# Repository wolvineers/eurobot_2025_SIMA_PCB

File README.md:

# eurobot_2025_SIMA_PCB
Repository of the eurobot 2025 SIMA's PCB

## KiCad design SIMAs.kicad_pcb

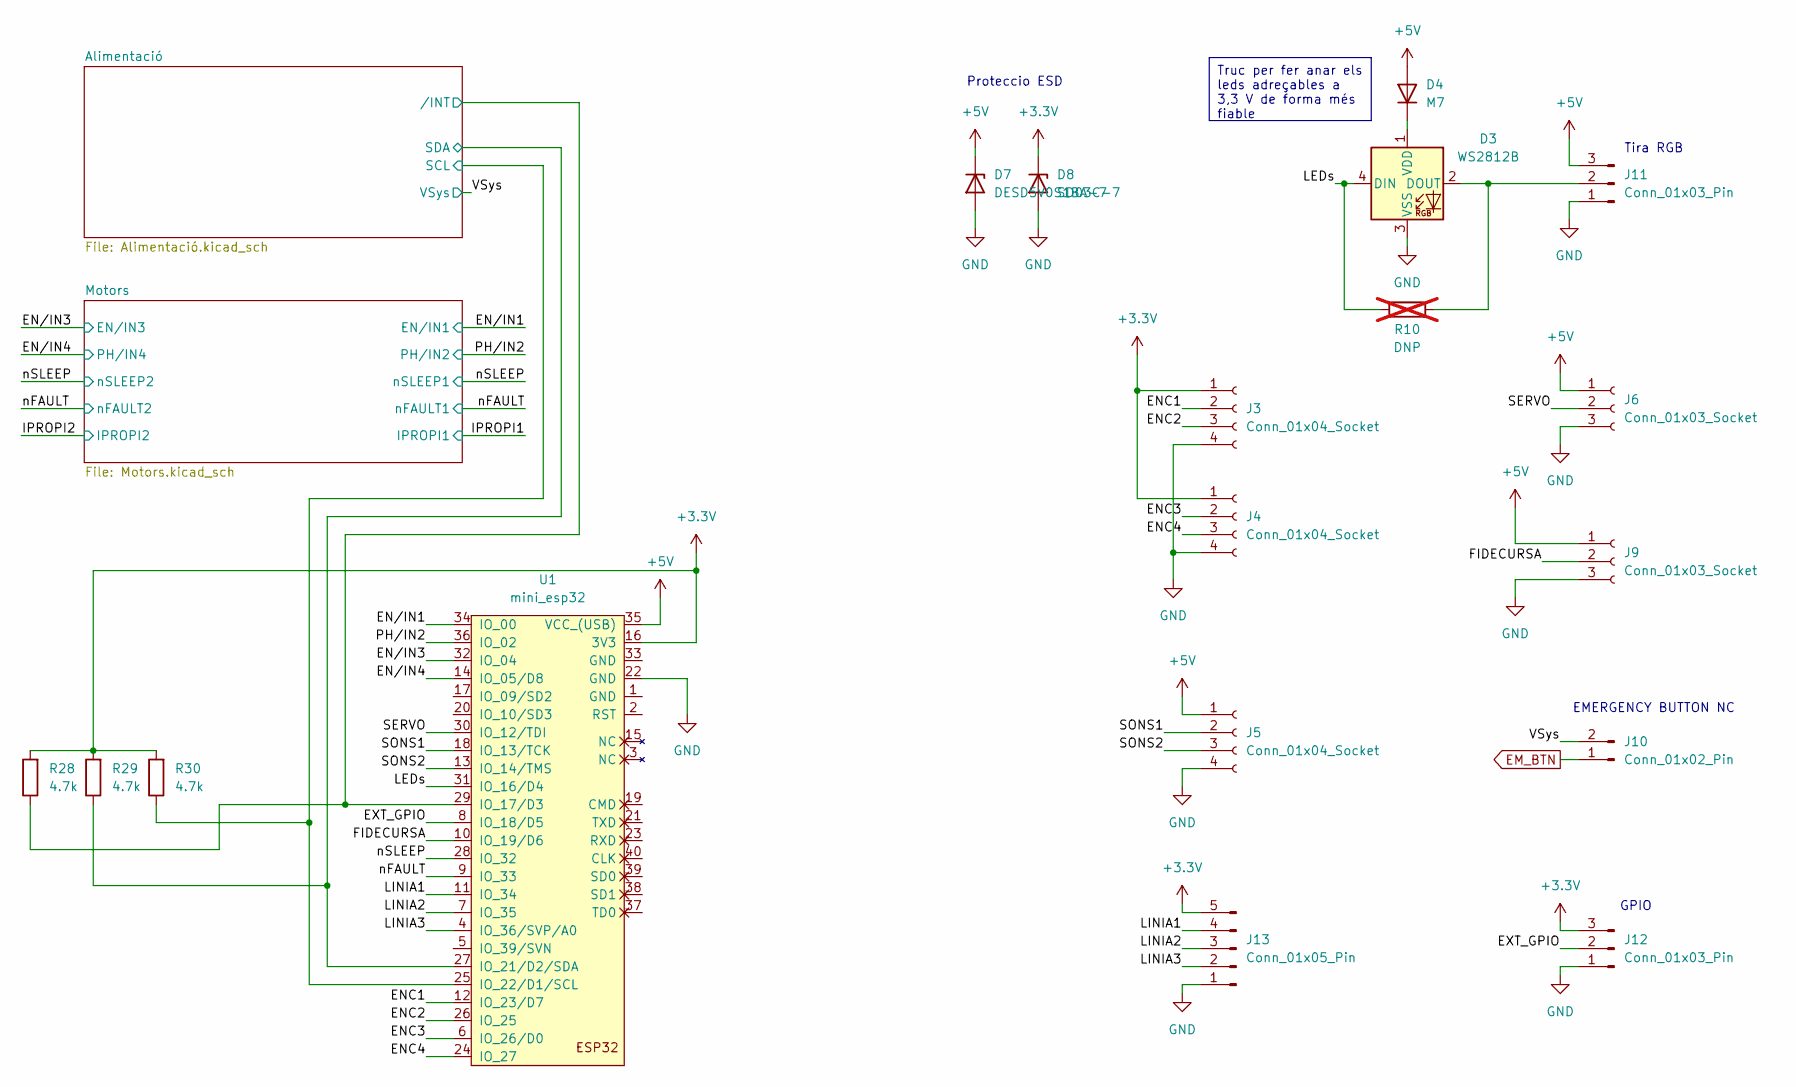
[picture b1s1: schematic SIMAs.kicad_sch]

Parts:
D3: WS2812B; LED_WS2812B_PLCC4_5.0x5.0mm_P3.2mm
D4: M7; D_SMA_Handsoldering
D7: DESD5V0S1BA-7; D_SOD-323
D8: SD03C-7; D_SOD-323
J3, J4, J5: Conn_01x04_Socket; JST_PH_B4B-PH-K_1x04_P2.00mm_Vertical
J6, J9: Conn_01x03_Socket; JST_PH_B3B-PH-K_1x03_P2.00mm_Vertical
J10: Conn_01x02_Pin; JST_PH_B2B-PH-K_1x02_P2.00mm_Vertical
J11, J12: Conn_01x03_Pin; JST_PH_B3B-PH-K_1x03_P2.00mm_Vertical
J13: Conn_01x05_Pin; JST_PH_B5B-PH-K_1x05_P2.00mm_Vertical
R10: DNP; R_0603_1608Metric; not fitted
R28, R29, R30: 4.7k; R_0603_1608Metric
U1: mini_esp32; ESP32_mini

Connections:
+3.3V: D8.1 (K), J3.1, J4.1, J12.3, J13.5, R28.2, R29.2, R30.2, U1.16 (3V3)
+5V: D4.2 (A), D7.1 (K), J5.1, J6.1, J9.1, J11.3, U1.35 (VCC_(USB)); also elsewhere on the board
/Alimentació/SCL: R30.1, U1.25 (IO_22/D1/SCL); also elsewhere on the board
/Alimentació/SDA: R29.1, U1.27 (IO_21/D2/SDA); also elsewhere on the board
/Alimentació//INT: R28.1, U1.29 (IO_17/D3); also elsewhere on the board
/ENC1: J3.2, U1.12 (IO_23/D7)
/ENC2: J3.3, U1.26 (IO_25)
/ENC3: J4.2, U1.6 (IO_26/D0)
/ENC4: J4.3, U1.24 (IO_27)
/EN/IN1: U1.34 (IO_00); also elsewhere on the board
/EN/IN3: U1.32 (IO_04); also elsewhere on the board
/EN/IN4: U1.14 (IO_05/D8); also elsewhere on the board
/EXT_GPIO: J12.2, U1.8 (IO_18/D5)
/FIDECURSA: J9.2, U1.10 (IO_19/D6)
/LEDs: D3.4 (DIN), R10.1, U1.31 (IO_16/D4)
/LINIA1: J13.4, U1.11 (IO_34)
/LINIA2: J13.3, U1.7 (IO_35)
/LINIA3: J13.2, U1.4 (IO_36/SVP/A0)
/PH/IN2: U1.36 (IO_02); also elsewhere on the board
/SERVO: J6.2, U1.30 (IO_12/TDI)
/SONS1: J5.2, U1.18 (IO_13/TCK)
/SONS2: J5.3, U1.13 (IO_14/TMS)
/VSys: J10.2; also elsewhere on the board
/nFAULT: U1.9 (IO_33); also elsewhere on the board
/nSLEEP: U1.28 (IO_32); also elsewhere on the board
EM_BTN: J10.1; also elsewhere on the board
GND: D3.3 (VSS), D7.2 (A), D8.2 (A), J3.4, J4.4, J5.4, J6.3, J9.3, J11.1, J12.1, J13.1, U1.22 (GND); also elsewhere on the board
unnamed: D3.2 (DOUT), J11.2, R10.2
unnamed: D3.1 (VDD), D4.1 (K)

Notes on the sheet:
Truc per fer anar els leds adreçables a 3,3 V de forma més fiable
EMERGENCY BUTTON NC
GPIO
Tira RGB
Proteccio ESD

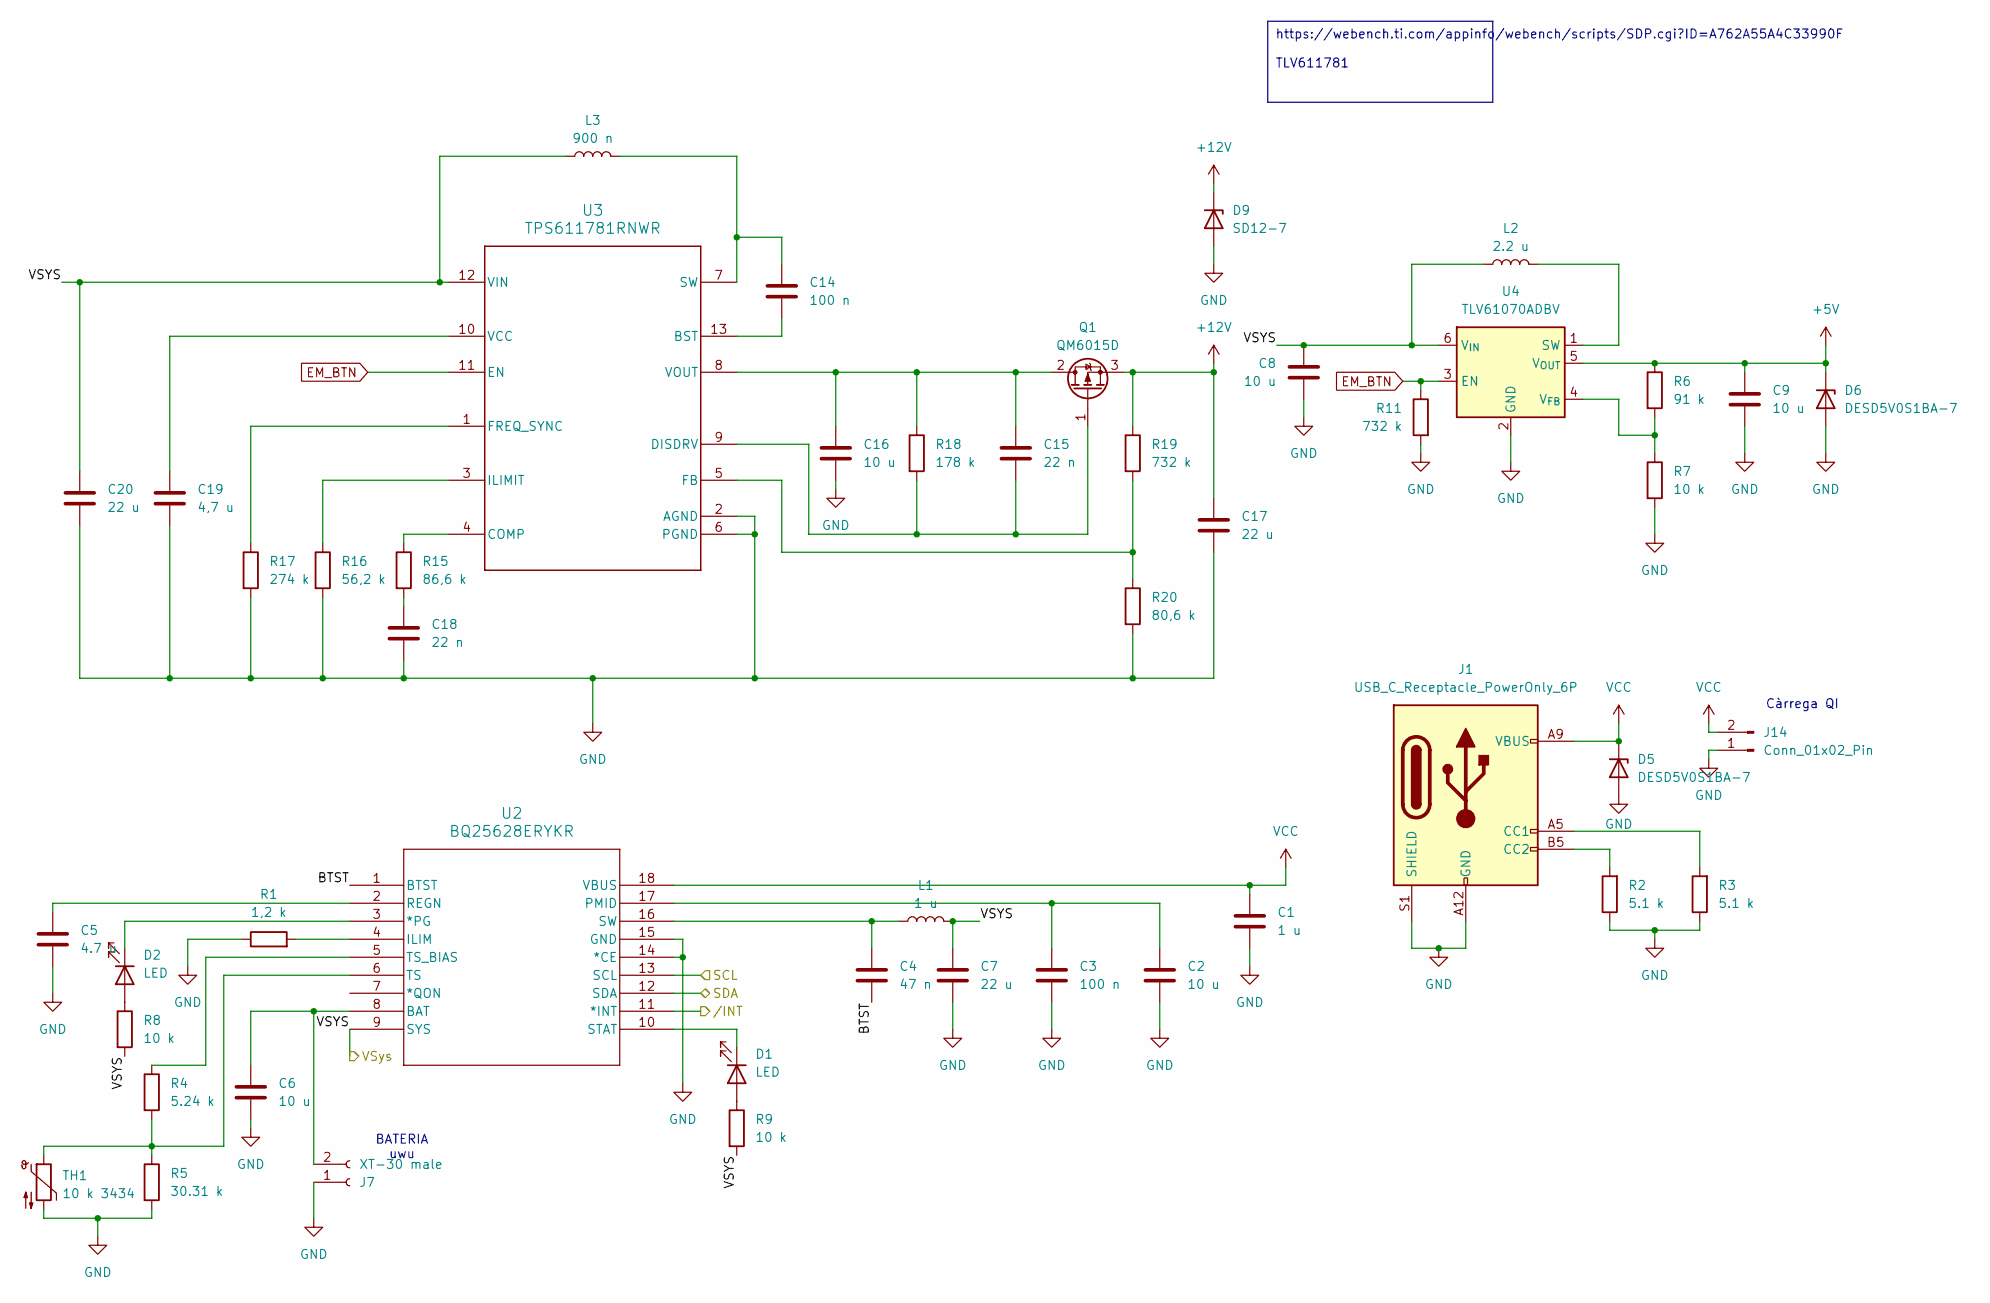
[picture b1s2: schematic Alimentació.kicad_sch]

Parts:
C1: 1 u; C_0603_1608Metric_Pad1.08x0.95mm_HandSolder
C2, C6, C8, C9, C16: 10 u; C_0603_1608Metric_Pad1.08x0.95mm_HandSolder
C3, C14: 100 n; C_0603_1608Metric_Pad1.08x0.95mm_HandSolder
C4: 47 n; C_0603_1608Metric_Pad1.08x0.95mm_HandSolder
C5: 4.7 u; C_0603_1608Metric_Pad1.08x0.95mm_HandSolder
C7, C17, C20: 22 u; C_0603_1608Metric_Pad1.08x0.95mm_HandSolder
C15, C18: 22 n; C_0603_1608Metric_Pad1.08x0.95mm_HandSolder
C19: 4,7 u; C_0603_1608Metric_Pad1.08x0.95mm_HandSolder
D1, D2: LED; D_0603_1608Metric
D5, D6: DESD5V0S1BA-7; D_SOD-323
D9: SD12-7; D_SOD-323
J1: USB_C_Receptacle_PowerOnly_6P; USB_C_6_DEALON
J7: XT-30 male; AMASS_XT30U-M_1x02_P5.0mm_Vertical
J14: Conn_01x02_Pin; JST_PH_B2B-PH-K_1x02_P2.00mm_Vertical
L1: 1 u; L_1008_2520Metric_Pad1.43x2.20mm_HandSolder
L2: 2.2 u; L_1008_2520Metric_Pad1.43x2.20mm_HandSolder
L3: 900 n; L_1008_2520Metric_Pad1.43x2.20mm_HandSolder
Q1: QM6015D; TO-252-2
R1: 1,2 k; R_0603_1608Metric
R2, R3: 5.1 k; R_0603_1608Metric
R4: 5.24 k; R_0603_1608Metric
R5: 30.31 k; R_0603_1608Metric
R6: 91 k; R_0603_1608Metric
R7, R8, R9: 10 k; R_0603_1608Metric
R11, R19: 732 k; R_0603_1608Metric
R15: 86,6 k; R_0603_1608Metric
R16: 56,2 k; R_0603_1608Metric
R17: 274 k; R_0603_1608Metric
R18: 178 k; R_0603_1608Metric
R20: 80,6 k; R_0603_1608Metric
TH1: 10 k 3434; R_0603_1608Metric_Pad0.98x0.95mm_HandSolder
U2: BQ25628ERYKR; WQFN-HR18__RYK_TEX
U3: TPS611781RNWR; RNW0013A
U4: TLV61070ADBV; SOT-23-6

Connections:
+5V: C9.1, D6.1 (K), R6.1, U4.5 (V_{OUT}); also elsewhere on the board
+12V: C17.1, D9.1 (K), Q1.3 (S), R19.1; also elsewhere on the board
/Alimentació/BTST: C4.2, U2.1 (BTST)
/Alimentació/SCL: U2.13 (SCL); also elsewhere on the board
/Alimentació/SDA: U2.12 (SDA); also elsewhere on the board
/Alimentació//INT: U2.11 (*INT); also elsewhere on the board
/VSys: C7.1, C8.1, C20.1, L1.2, L2.1, L3.1, R8.2, R9.2, U2.9 (SYS), U3.12 (VIN), U4.6 (V_{IN}); also elsewhere on the board
EM_BTN: R11.1, U3.11 (EN), U4.3 (EN); also elsewhere on the board
GND: C1.1, C2.2, C3.2, C5.2, C6.2, C7.2, C8.2, C9.2, C16.2, C17.2, C18.2, C19.2, C20.2, D5.2 (A), D6.2 (A), D9.2 (A), J1.A12 (GND), J1.B12 (GND), J1.S1 (SHIELD), J7.1, J14.1, R1.1, R2.1, R3.1, R5.2, R7.2, R11.2, R16.2, R17.2, R20.2, TH1.2, U2.14 (*CE), U2.15 (GND), U3.2 (AGND), U3.6 (PGND), U4.2 (GND); also elsewhere on the board
unnamed: C18.1, R15.2
unnamed: D1.2 (A), R9.1
unnamed: D1.1 (K), U2.10 (STAT)
unnamed: D2.2 (A), R8.1
unnamed: D2.1 (K), U2.3 (*PG)
unnamed: J1.A5 (CC1), R3.2
unnamed: J1.B5 (CC2), R2.2
unnamed: C6.1, J7.2, U2.8 (BAT)
unnamed: C15.1, C16.1, Q1.2 (D), R18.1, U3.8 (VOUT)
unnamed: C15.2, Q1.1 (G), R18.2, U3.9 (DISDRV)
unnamed: R1.2, U2.4 (ILIM)
unnamed: C2.1, C3.1, U2.17 (PMID)
unnamed: C5.1, U2.2 (REGN)
unnamed: C4.1, L1.1, U2.16 (SW)
unnamed: R4.2, R5.1, TH1.1, U2.6 (TS)
unnamed: R4.1, U2.5 (TS_BIAS)
unnamed: C14.2, U3.13 (BST)
unnamed: R15.1, U3.4 (COMP)
unnamed: R19.2, R20.1, U3.5 (FB)
unnamed: R17.1, U3.1 (FREQ_SYNC)
unnamed: R16.1, U3.3 (ILIMIT)
unnamed: C14.1, L3.2, U3.7 (SW)
unnamed: C19.1, U3.10 (VCC)
unnamed: L2.2, U4.1 (SW)
unnamed: R6.2, R7.1, U4.4 (V_{FB})
VCC: C1.2, D5.1 (K), J1.A9 (VBUS), J1.B9 (VBUS), J14.2, U2.18 (VBUS)

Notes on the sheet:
https://webench.ti.com/appinfo/webench/scripts/SDP.cgi?ID=A762A55A4C33990F TLV611781
Càrrega QI
BATERIA uwu

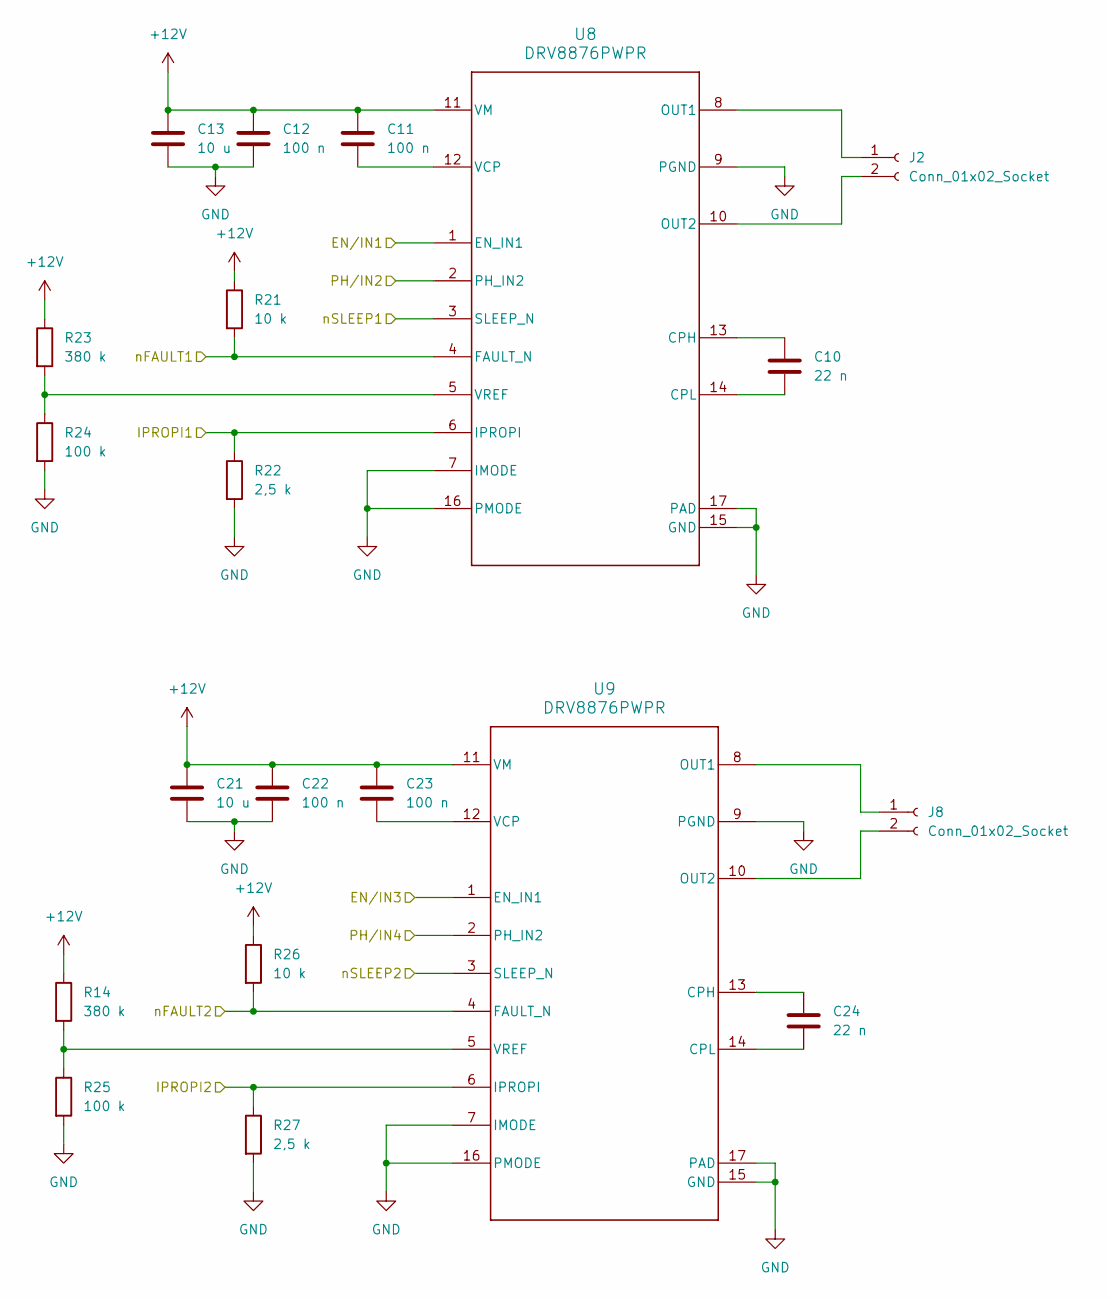
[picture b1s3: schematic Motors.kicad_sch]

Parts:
C10, C24: 22 n; C_0603_1608Metric_Pad1.08x0.95mm_HandSolder
C11, C12, C22, C23: 100 n; C_0603_1608Metric_Pad1.08x0.95mm_HandSolder
C13, C21: 10 u; C_0603_1608Metric_Pad1.08x0.95mm_HandSolder
J2, J8: Conn_01x02_Socket; JST_PH_B2B-PH-K_1x02_P2.00mm_Vertical
R14, R23: 380 k; R_0603_1608Metric
R21, R26: 10 k; R_0603_1608Metric
R22, R27: 2,5 k; R_0603_1608Metric
R24, R25: 100 k; R_0603_1608Metric
U8, U9: DRV8876PWPR; PWP0016J_N

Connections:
+12V: C11.2, C12.1, C13.1, C21.1, C22.1, C23.2, R14.1, R21.1, R23.1, R26.1, U8.11 (VM), U9.11 (VM); also elsewhere on the board
/EN/IN1: U8.1 (EN_IN1); also elsewhere on the board
/EN/IN3: U9.1 (EN_IN1); also elsewhere on the board
/EN/IN4: U9.2 (PH_IN2); also elsewhere on the board
/IPROPI1: R22.1, U8.6 (IPROPI)
/IPROPI2: R27.1, U9.6 (IPROPI)
/PH/IN2: U8.2 (PH_IN2); also elsewhere on the board
/nFAULT: R21.2, R26.2, U8.4 (FAULT_N), U9.4 (FAULT_N); also elsewhere on the board
/nSLEEP: U8.3 (SLEEP_N), U9.3 (SLEEP_N); also elsewhere on the board
GND: C12.2, C13.2, C21.2, C22.2, R22.2, R24.2, R25.2, R27.2, U8.7 (IMODE), U8.9 (PGND), U8.15 (GND), U8.16 (PMODE), U8.17 (PAD), U9.7 (IMODE), U9.9 (PGND), U9.15 (GND), U9.16 (PMODE), U9.17 (PAD); also elsewhere on the board
unnamed: J2.1, U8.8 (OUT1)
unnamed: J2.2, U8.10 (OUT2)
unnamed: J8.1, U9.8 (OUT1)
unnamed: J8.2, U9.10 (OUT2)
unnamed: C10.1, U8.13 (CPH)
unnamed: C10.2, U8.14 (CPL)
unnamed: C11.1, U8.12 (VCP)
unnamed: R23.2, R24.1, U8.5 (VREF)
unnamed: C24.1, U9.13 (CPH)
unnamed: C24.2, U9.14 (CPL)
unnamed: C23.1, U9.12 (VCP)
unnamed: R14.2, R25.1, U9.5 (VREF)

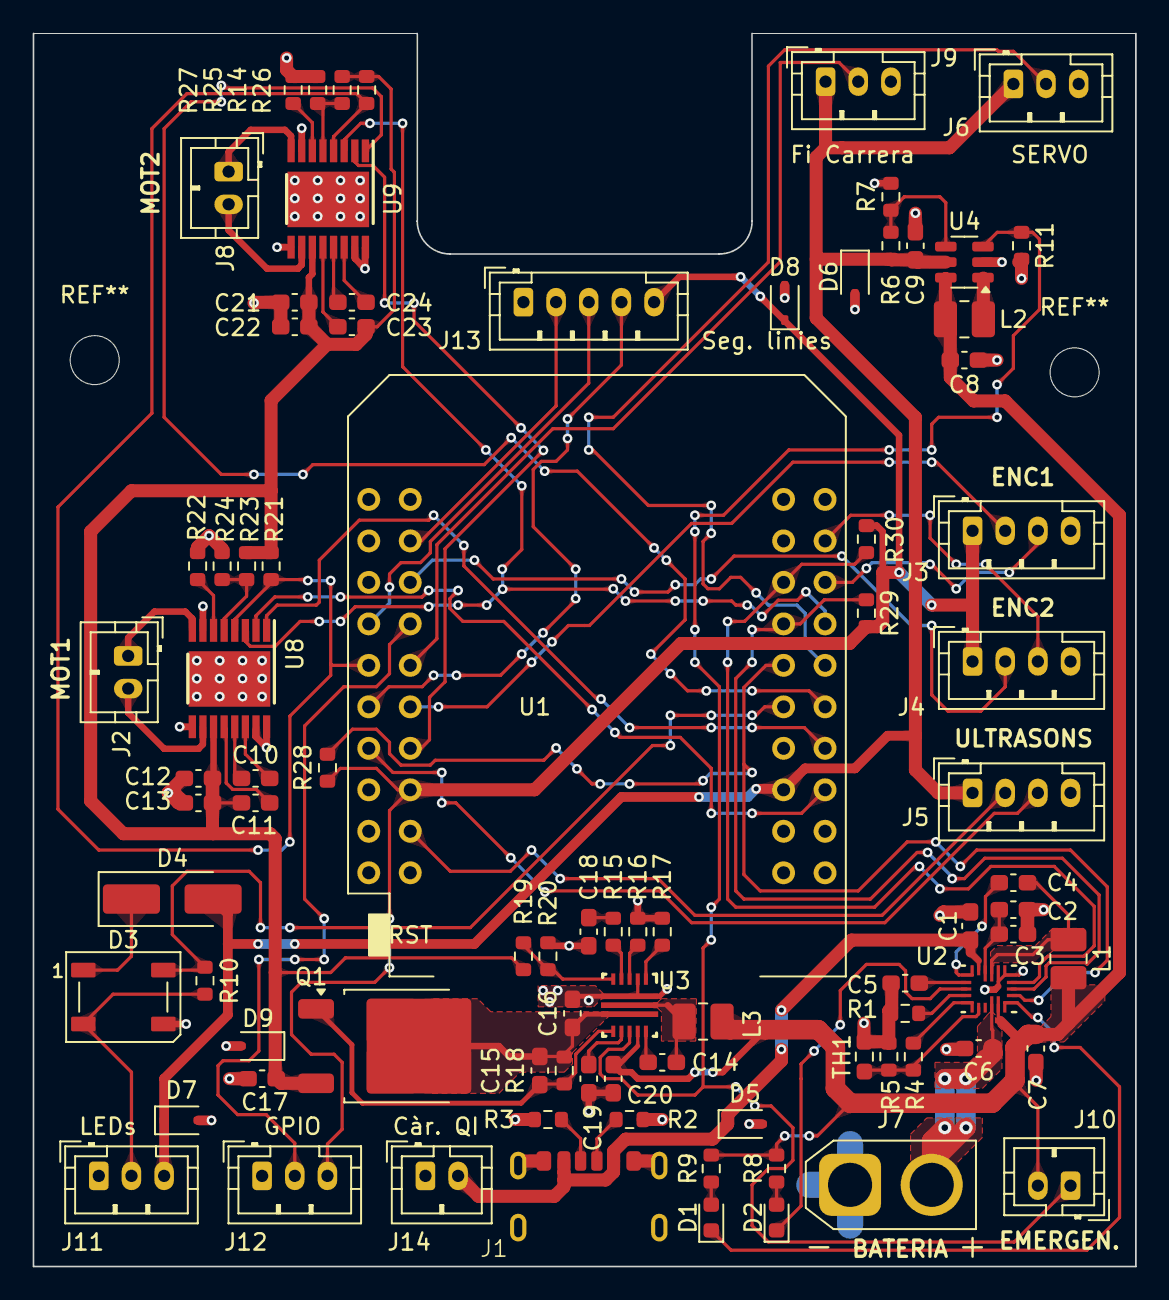
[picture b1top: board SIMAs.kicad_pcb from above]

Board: 2 copper layers, 67.5 x 75.5 mm, 86 parts (0 on the bottom side), 71 nets.

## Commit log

2024-12-14 Added the project files
    Added the project files, which were half done. Schematic only half done, no PCB.
2024-12-14 Battery charger and 5V boost
    Added a herarchical sheet for the poers supply. Done the battery charger and monitor schematic with USB-C charging and the 5 V boost.
2025-01-17 Canvi
    Algu ha canviat, no recordo
2025-01-25 actualitzar pcb main
2025-01-25 actualitzar pcb dev
2025-01-25 actualitzar ultrima versio pcb/esquematic
2025-01-25 arreclat footprints/symbol
2025-01-25 esquematic fet v1
2025-02-01 Col·locats tots els components
    S'han col·locat tots els components a la seva posició a la placa a més d'haver-ne afegit algun més.
2025-02-01 Pistes
    S'han fet les pistes i les connexions entre tots els components. Falta revisar-les.
2025-02-08 Revisio de la placa
    S'ha revisat la placa
2025-02-08 Silskreen
2025-02-08 Afegit avellanat i teardrops
    S'ha afegit avellanat en la cantonada interna de la placa per permetre la fabricació, i s'han afegit les llàgrimes a les pistes.
2025-02-08 Generats fitxers de fabricació per jlcpcb + ibom
    S'ha generat els fitxers de fabricació per jlcpcb (també serveix per altres), i s'ha generat el BOM en html per facilitar la producció a mà.
2025-02-08 Versió 1.0, inicial
    Versió 1.0, inicial, de la placa, amb els fitxers de producció.
2025-02-21 Actualitzats valors dels components
    S'han actualitzat els valors de components d'acord als comprats, s'ha canviat algun valor per conveniència, i s'ha acabat de donar valors a tots els components
2025-03-23 S'ha actualitzat la pcb amb els nous valors
    S'ha incorporat a la pcb els canvis anteriors a l'esquemàtic, i s'ha regenerat l'ibom.
2025-03-23 Nou esquemàtic
    Nou esquemàtic per bateria en sèrie de dues cèl·les, boost de 12 V extern, i buck de 5 V.
